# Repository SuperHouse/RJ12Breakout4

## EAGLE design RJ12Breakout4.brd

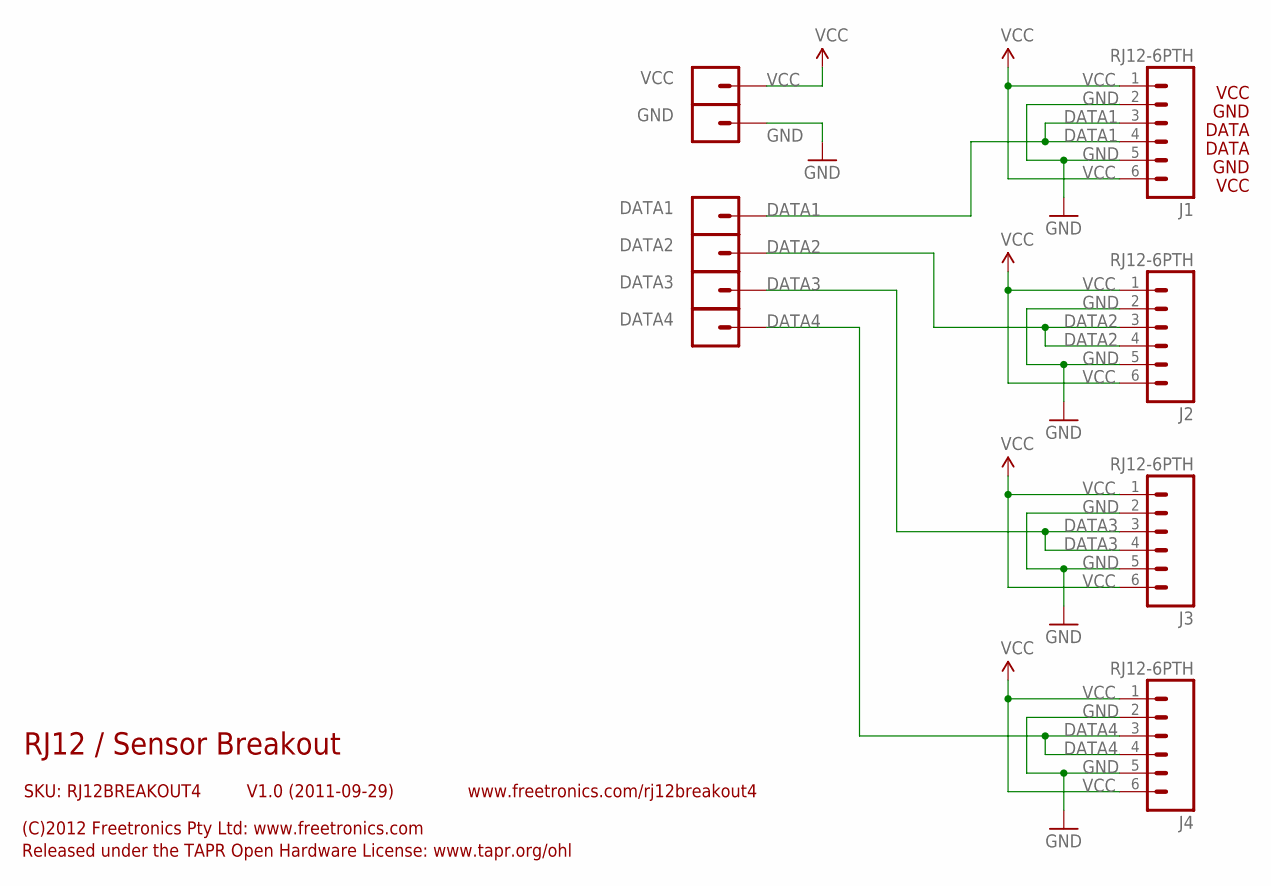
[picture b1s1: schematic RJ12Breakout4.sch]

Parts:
DATA1, DATA2, DATA3, DATA4: M01PTH; 1X01
GND: M01PTH; 1X01
J1, J2, J3, J4: RJ12-6PTH; RJ12-6
VCC: M01PTH; 1X01

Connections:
DATA1: DATA1.1, J1.3, J1.4
DATA2: DATA2.1, J2.3, J2.4
DATA3: DATA3.1, J3.3, J3.4
DATA4: DATA4.1, J4.3, J4.4
GND: GND.1, J1.2, J1.5, J2.2, J2.5, J3.2, J3.5, J4.2, J4.5
VCC: J1.1, J1.6, J2.1, J2.6, J3.1, J3.6, J4.1, J4.6, VCC.1

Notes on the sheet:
RJ12 / Sensor Breakout
V1.0 (2011-09-29)
SKU: RJ12BREAKOUT4
(C)2012 Freetronics Pty Ltd: www.freetronics.com
Released under the TAPR Open Hardware License: www.tapr.org/ohl
www.freetronics.com/rj12breakout4
VCC
DATA
GND

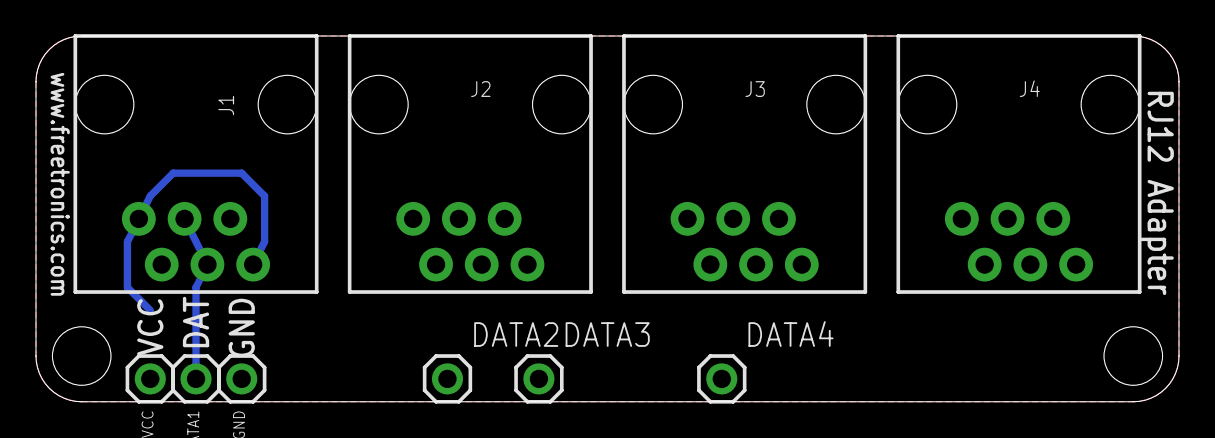
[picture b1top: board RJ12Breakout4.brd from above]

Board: 2 copper layers, 63.5 x 20.3 mm, 10 parts (0 on the bottom side), 6 nets.

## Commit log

2019-04-24 Imported old project files

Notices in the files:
parts and their libraries:
freetronics-original: Licensing: CC v3.0 Share-Alike You are welcome to use this library for commercial purposes.
